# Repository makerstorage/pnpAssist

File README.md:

<!-- PROJECT LOGO 
<br />
<p align="center">
  
-->
  <h3 align="center">PnPAssist</h3>

<!-- ABOUT THE PROJECT -->
## Description
The PnPAssist is an open source innovative CNC table that position the next SMT component with a proper orientation for you to make hand assembly a lot more fun and way more efficient.

PnPAssist is a numerical, precise positioning device that makes tedious and repetitive manual PCB assembly easier for you and prevents you from making mistakes.

<!-- LICENSE -->
## License

GNU GENERAL PUBLIC LICENSE Version 3, 29 June 2007 See `LICENSE` for more information.

<!-- CONTRIBUTING -->
## Contributing

Contributions are what make the open source community such an amazing place to be learn, inspire, and create. Any contributions you make are **greatly appreciated**.

1. Fork the Project
2. Create your Feature Branch (`git checkout -b feature/AmazingFeature`)
3. Commit your Changes (`git commit -m 'Add some AmazingFeature'`)
4. Push to the Branch (`git push origin feature/AmazingFeature`)
5. Open a Pull Request

<!-- CONTACT -->
## Contact

Nuri Erginer - [@nerginer](https://twitter.com/nerginer) 
email - ne@makerstorage.com
Project Link: [Hackaday.io](https://hackaday.io/project/179878-pnpassist)

MakerStorage invests time and resources providing this open source design, please support MakerStorage and open-source hardware by purchasing products from MakerStorage!

Designed by MakerStorage LLC.

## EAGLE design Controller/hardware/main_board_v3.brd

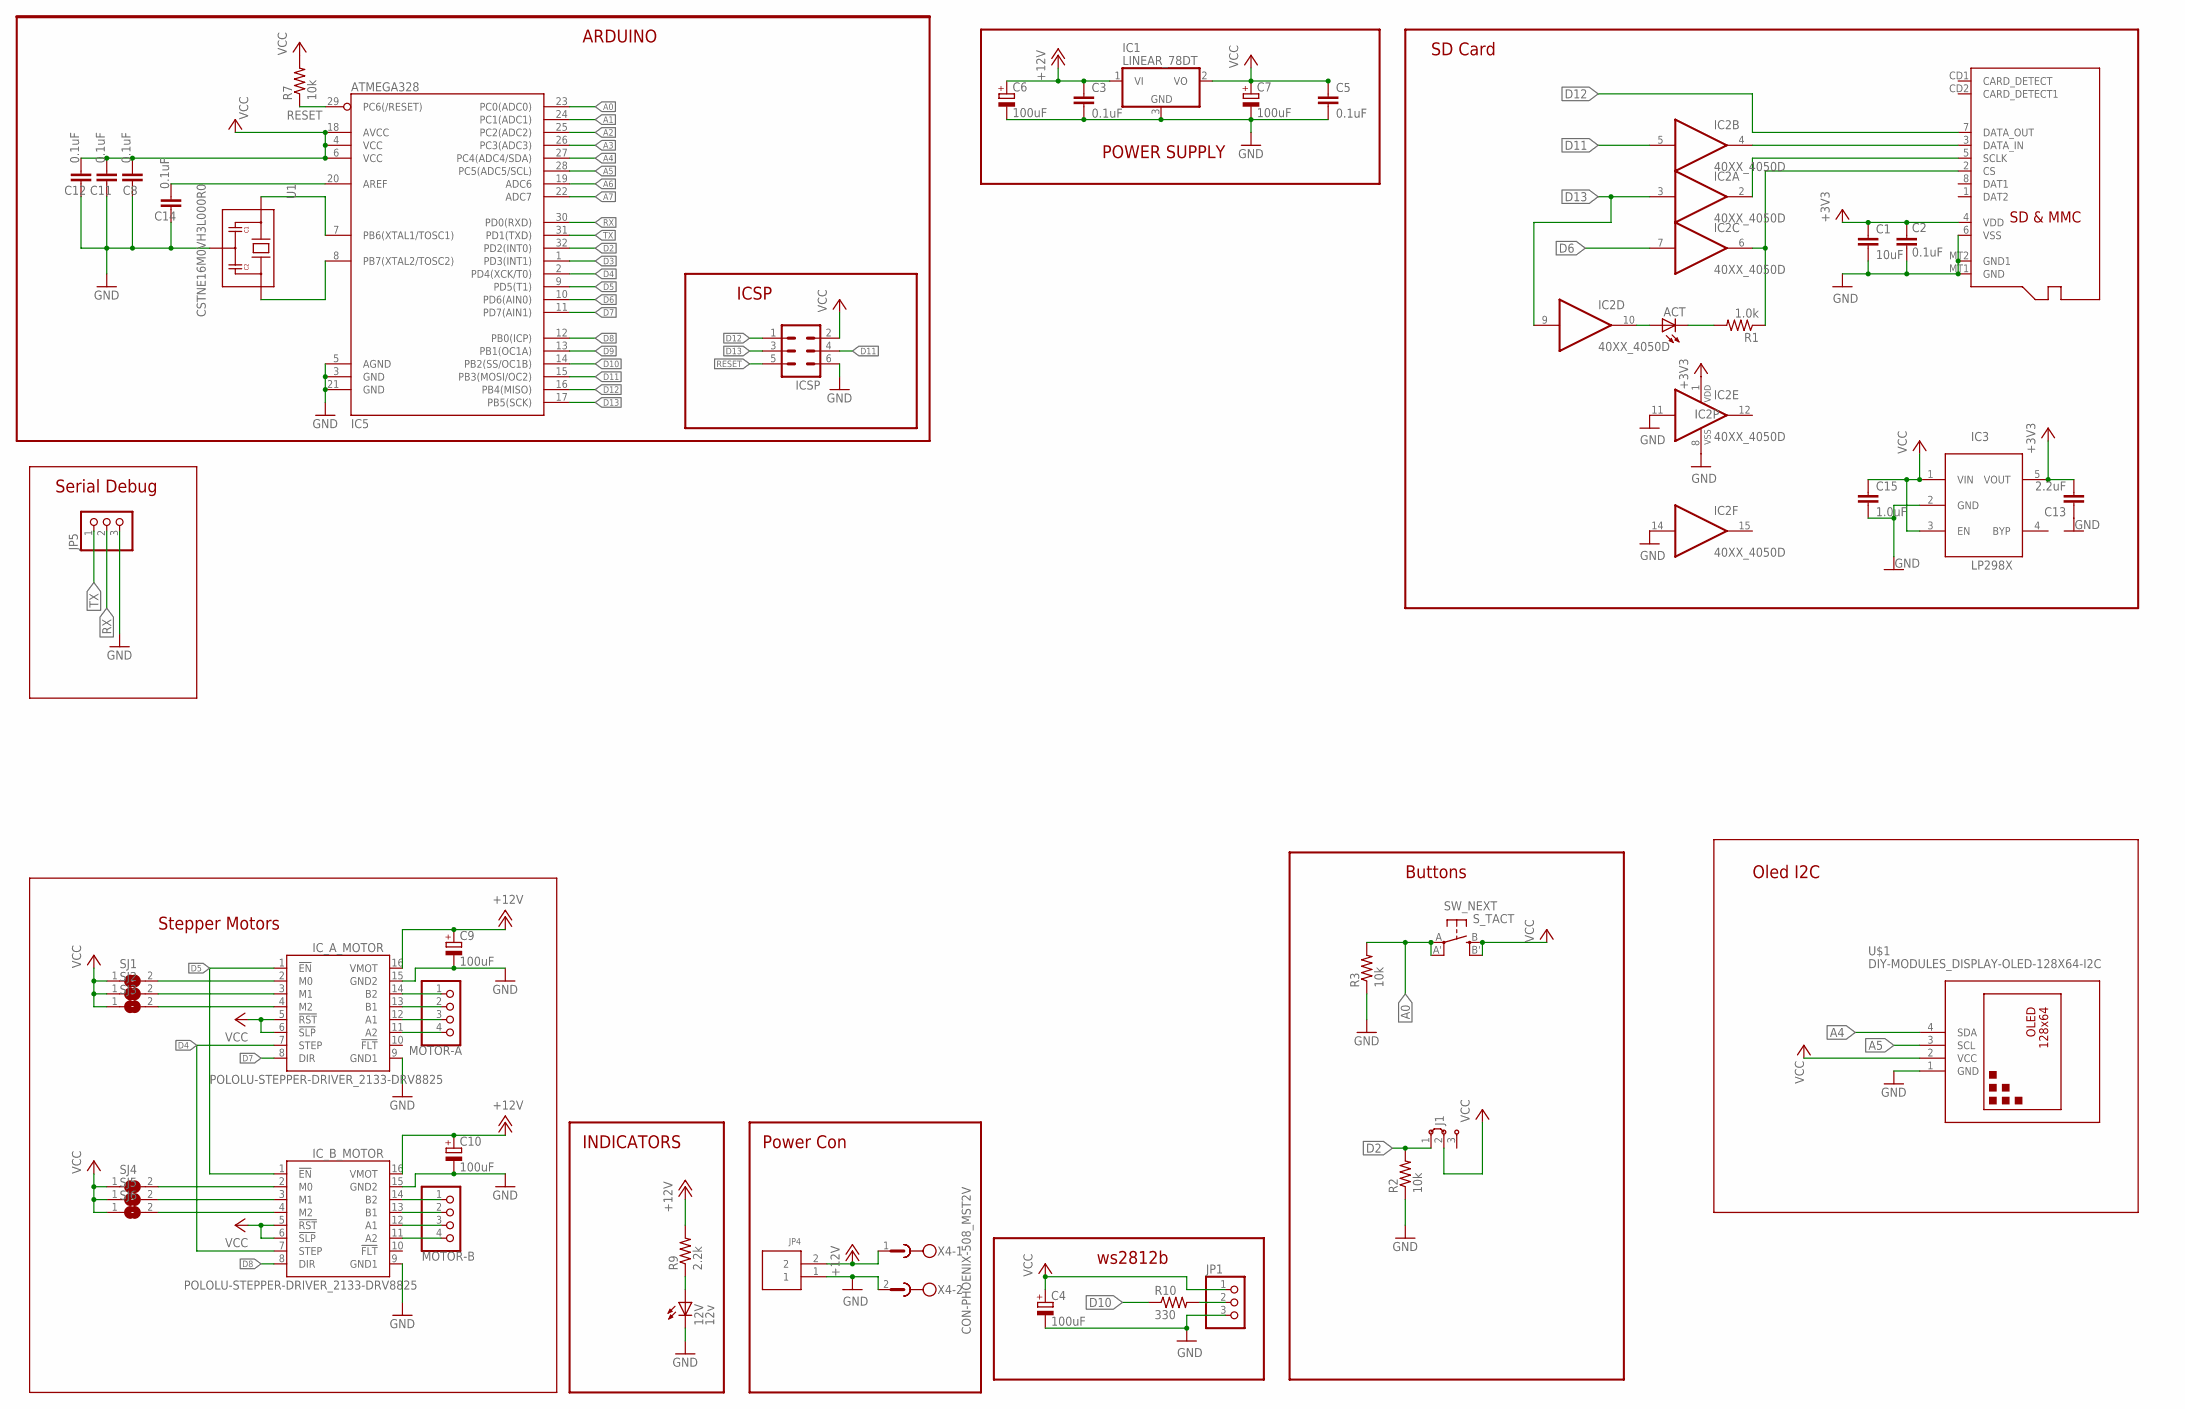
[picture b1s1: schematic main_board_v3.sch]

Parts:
12V: 12v; SPARKFUN_LED-0805
ACT: ACT; SPARKFUN_LED-0805
C1: 10uF; SPARKFUN_0805
C2, C3, C5, C8, C11, C12, C14: 0.1uF; SPARKFUN_0805
C4, C6, C7, C9, C10: 100uF; RCL_E3,5-8
C13: 2.2uF; SPARKFUN_0805
C15: 1.0uF; SPARKFUN_0805
IC1: LINEAR_78DT; LINEAR_TO252
IC2: 40XX_4050D; 40XX_SO16
IC3: LP298XS; ADAFRUIT_SOT23-5L
IC5: ATMEGA328; SPARKFUN_TQFP32-08
ICSP: CON-HARTING-ML_ML6
IC_A_MOTOR: POLOLU-STEPPER-DRIVER_2133-DRV8825; POLOLU-STEPPER-DRIVER_DRV8825
IC_B_MOTOR: POLOLU-STEPPER-DRIVER_2133-DRV8825; POLOLU-STEPPER-DRIVER_DRV8825
J1: JUMPER_J2X5MM; JUMPER_05C
JP1, JP5: ADAFRUIT_PINHD-1X3; ADAFRUIT_1X03
JP4: JST_EPH_2PIN; JST_EPH_B2B-PH-K-S
MOTOR-A: PINHD-1X4; 1X04
MOTOR-B: PINHD-1X4; 1X04
R1: 1.0k; ADAFRUIT_R0805
R2, R3, R7: 10k; ADAFRUIT_R0805
R9: 2.2k; ADAFRUIT_R0805
R10: 330; ADAFRUIT_R0805
SJ1, SJ2, SJ3, SJ4, SJ5, SJ6: JUMPER_SJ
SW_NEXT: S_TACT; ADAFRUIT_EVQ-Q2
U1: CSTNE16M0VH3L000R0; XTAL_CSTNE16M0VH3L000R0
U$1: DIY-MODULES_DISPLAY-OLED-128X64-I2C
X1: MICROSD_SMD; ADAFRUIT_MICROSD
X4: CON-PHOENIX-508_MST2V; CON-PHOENIX-508_MSTBV2

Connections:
+3V3: C1.1, C2.1, C13.2, IC2.1 (VDD), IC3.5 (VOUT), X1.4 (VDD)
+12V: C3.1, C6.+, C9.+, C10.+, IC1.1 (VI), IC_A_MOTOR.16 (VMOT), IC_B_MOTOR.16 (VMOT), JP4.2, R9.2, X4.1
A0: IC5.23 (PC0(ADC0)), R3.2, SW_NEXT.A, SW_NEXT.A' (P1)
A1: IC5.24 (PC1(ADC1))
A2: IC5.25 (PC2(ADC2))
A3: IC5.26 (PC3(ADC3))
A4: IC5.27 (PC4(ADC4/SDA)), U$1.4 (SDA)
A5: IC5.28 (PC5(ADC5/SCL)), U$1.3 (SCL)
A6: IC5.19 (ADC6)
A7: IC5.22 (ADC7)
D2: IC5.32 (PD2(INT0)), J1.1, R2.2
D3: IC5.1 (PD3(INT1))
D4: IC5.2 (PD4(XCK/T0)), IC_A_MOTOR.7 (STEP), IC_B_MOTOR.7 (STEP)
D5: IC5.9 (PD5(T1)), IC_A_MOTOR.1 (!EN), IC_B_MOTOR.1 (!EN)
D6: IC2.7 (I), IC5.10 (PD6(AIN0))
D7: IC5.11 (PD7(AIN1)), IC_A_MOTOR.8 (DIR)
D8: IC5.12 (PB0(ICP)), IC_B_MOTOR.8 (DIR)
D9: IC5.13 (PB1(OC1A))
D10: IC5.14 (PB2(SS/OC1B)), R10.1
D11: IC2.5 (I), IC5.15 (PB3(MOSI/OC2)), ICSP.4
D12: IC5.16 (PB4(MISO)), ICSP.1, X1.7 (DATA_OUT)
D13: IC2.3 (I), IC2.9 (I), IC5.17 (PB5(SCK)), ICSP.3
GND: 12V.C, C1.2, C2.2, C3.2, C4.-, C5.2, C6.-, C7.-, C8.1, C9.-, C10.-, C11.1, C12.1, C13.1, C14.1, C15.2, IC1.3 (GND), IC2.8 (VSS), IC2.11 (I), IC2.14 (I), IC3.2 (GND), IC5.3 (GND), IC5.5 (AGND), IC5.21 (GND), ICSP.6, IC_A_MOTOR.9 (GND1), IC_A_MOTOR.15 (GND2), IC_B_MOTOR.9 (GND1), IC_B_MOTOR.15 (GND2), JP1.3, JP4.1, JP5.3, R2.1, R3.1, U1.2 (GND), U$1.1 (GND), X1.6 (VSS), X1.MT1 (GND), X1.MT2 (GND1), X4.2
unnamed: ACT.A, IC2.10 (O)
unnamed: IC2.2 (O), X1.5 (SCLK)
unnamed: IC2.6 (O), R1.1, X1.2 (CS)
unnamed: ACT.C, R1.2
unnamed: IC2.4 (O), X1.3 (DATA_IN)
unnamed: JP1.2, R10.2
unnamed: IC_A_MOTOR.2 (M0), SJ1.2
unnamed: IC_A_MOTOR.3 (M1), SJ2.2
unnamed: IC_A_MOTOR.4 (M2), SJ3.2
unnamed: IC_B_MOTOR.2 (M0), SJ4.2
unnamed: IC_B_MOTOR.3 (M1), SJ5.2
unnamed: IC_B_MOTOR.4 (M2), SJ6.2
unnamed: IC_A_MOTOR.14 (B2), MOTOR-A.1
unnamed: IC_A_MOTOR.13 (B1), MOTOR-A.2
unnamed: IC_A_MOTOR.12 (A1), MOTOR-A.3
unnamed: IC_A_MOTOR.11 (A2), MOTOR-A.4
unnamed: IC_B_MOTOR.14 (B2), MOTOR-B.1
unnamed: IC_B_MOTOR.13 (B1), MOTOR-B.2
unnamed: IC_B_MOTOR.12 (A1), MOTOR-B.3
unnamed: C14.2, IC5.20 (AREF)
unnamed: IC_B_MOTOR.11 (A2), MOTOR-B.4
unnamed: IC5.7 (PB6(XTAL1/TOSC1)), U1.1 (IN)
unnamed: IC5.8 (PB7(XTAL2/TOSC2)), U1.3 (OUT)
unnamed: 12V.A, R9.1
RESET: IC5.29 (PC6(/RESET)), ICSP.5, R7.1
RX: IC5.30 (PD0(RXD)), JP5.2
TX: IC5.31 (PD1(TXD)), JP5.1
VCC: C4.+, C5.1, C7.+, C8.2, C11.2, C12.2, C15.1, IC1.2 (VO), IC3.1 (VIN), IC3.3 (EN), IC5.4 (VCC), IC5.6 (VCC), IC5.18 (AVCC), ICSP.2, IC_A_MOTOR.5 (!RST), IC_A_MOTOR.6 (!SLP), IC_B_MOTOR.5 (!RST), IC_B_MOTOR.6 (!SLP), J1.2, JP1.1, R7.2, SJ1.1, SJ2.1, SJ3.1, SJ4.1, SJ5.1, SJ6.1, SW_NEXT.B (S), SW_NEXT.B' (S1), U$1.2 (VCC)

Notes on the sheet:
ICSP
ARDUINO
INDICATORS
POWER SUPPLY
Power Con
SD Card
Buttons
ws2812b
Oled I2C
Stepper Motors
Serial Debug

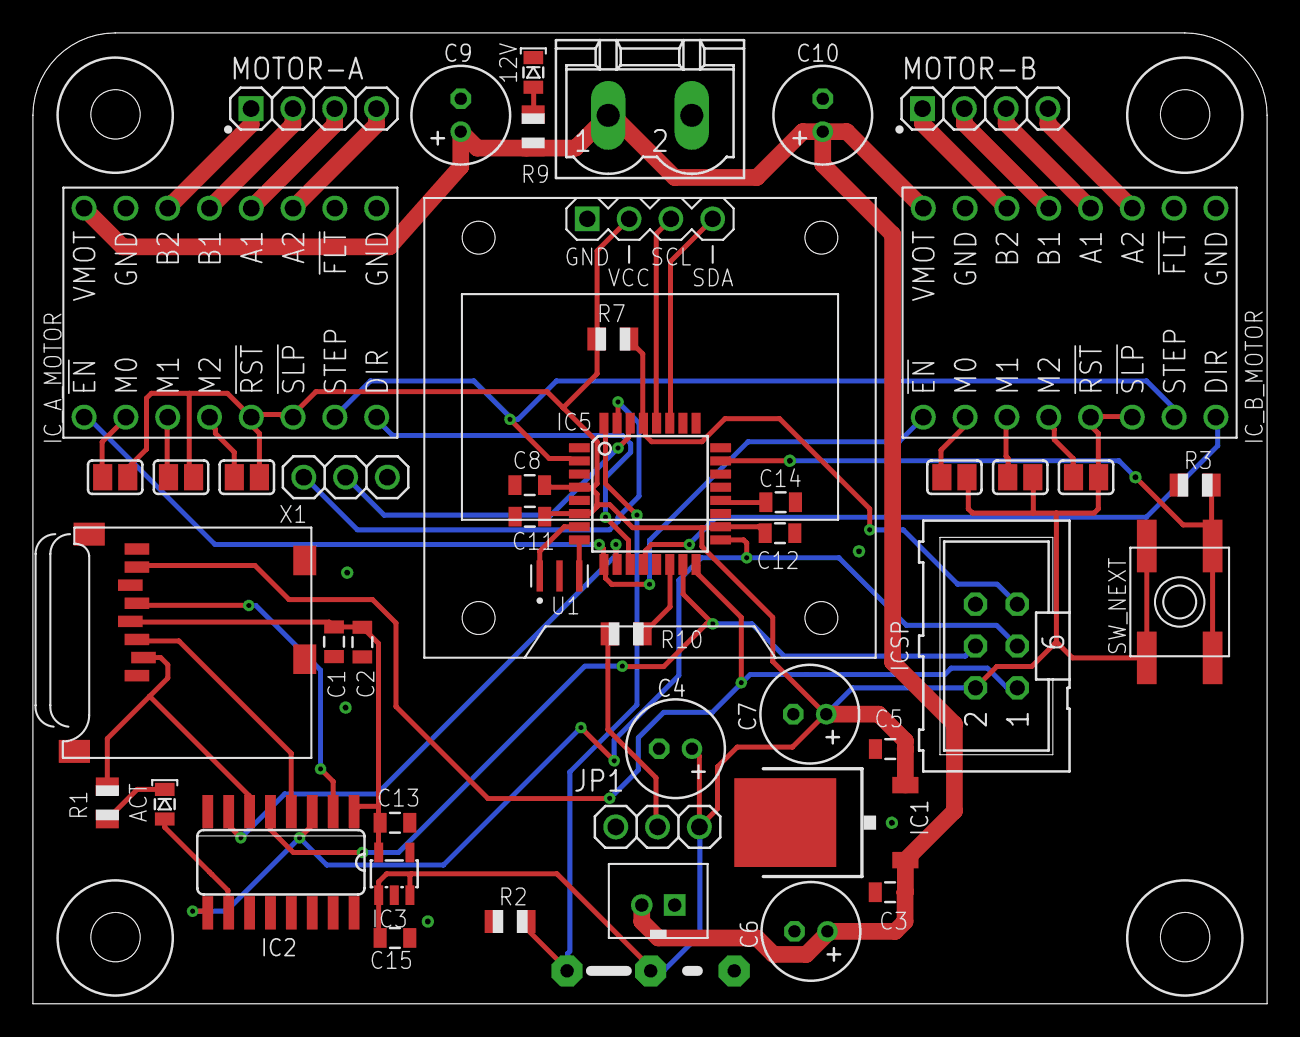
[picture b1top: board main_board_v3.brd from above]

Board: 2 copper layers, 75.0 x 59.0 mm, 47 parts (0 on the bottom side), 44 nets.

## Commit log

2021-06-12 firmware controller added
2021-06-12 gitignore
2021-06-13 nothing
2021-06-14 homing
2021-06-14 homing min
2021-06-15 images
2021-06-16 offsets deleted
2021-06-20 minor
2021-07-15 Next Button Code Changed
2021-07-15 two axis homing
2021-07-18 machine y offset set after new bearing
2021-07-19 changed th rotary axis direction
2021-07-22 3D Files
2021-07-24 main gear design v2
2021-07-26 2d files added
2021-07-26 read me
2021-07-26 read me2
2021-07-26 read me3
2021-07-26 Dxf version update
2021-07-29 knobs added to 3d files
2021-07-29 step files added to 3d files
2021-08-30 rulman_tut_orta file updated
2021-09-04 v2 firmware
2021-09-05 CONTRIBUTING.md added
2021-09-05 delay added to button wait code
2021-09-17 changed part reference to project specific library and updated capacitor parts
    updated capacitor parts with part numbers
2021-09-18 added part numbers, consolidated parts, cleaned up board/schematic
    added part numbers for capacitors, resistors, ic's and the main 12v connector.
    cleaned up the board layout a little, mainly just straightening traces.
    fixed the through hole 100uf cap footprint to reflect the bom part, 2mm leads 5mm body
    made both leds the same part number.
    removed the polarized caps from the sd card and replaced with smd 0805 ceramic caps.
    cleaned up the schematic a little and added a frame
2021-09-18 fixed a few silkscreen mistakes
2021-09-18 final cleanup
    little more silk screen shuffling and clearing DRC errors
2021-09-18 silkscreen on mount holes for washer clearance
2021-09-18 new 16mhz crystal with internal caps
2021-09-18 working bypass capacitors
    added bypass caps to the atmega328 and the 3v3 ldo per the datasheet. on the board relocated the 5v ldo bypass caps to be near the device itself.
2021-09-18 changed motor connectors
    changed motor connectors to .1" pitch 4 pos headers. the stepper motor stock connectors press nicely onto these. so if one wanted to they could just pins instead of soldering wires directly to the bo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
2021-09-18 moved 12v indicator next to power source
    moved the led next to the screw terminals. I have found people seem to like being able to see if a specific connection is getting power or not rather than having to look around on the board for an in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
2021-09-18 cleaned up traces
    finishing up this round of board improvements by cleaning up some traces
2021-09-19 bom and silkscreen updates
    bom information added to all the parts and the silkscreen was all normalized to 40mils and placed so there is no more overlapping. a few designators were missing from the board so i brought them back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
2021-09-19 updated board name
    changed board name to reflect copper changes
2021-09-19 updated board name
    updated board name while retaining the original board design files
2021-09-21 v2 stl files, assembly_manual_2d files_custom_shaft added
2021-09-22 step files added
2022-01-03 rotator updated
2022-01-05 kicad plugin added
